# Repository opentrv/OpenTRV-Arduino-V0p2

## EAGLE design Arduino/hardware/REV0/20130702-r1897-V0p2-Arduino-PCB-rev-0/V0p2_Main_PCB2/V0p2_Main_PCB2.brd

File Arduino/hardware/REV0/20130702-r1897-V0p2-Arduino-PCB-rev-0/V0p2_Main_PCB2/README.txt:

Using ATmega pinout for Eagle from:
http://www.faludi.com/2008/10/07/arduino-avr-library-for-eagle-layout-editor/
without explicit licence but following email permission:

    From: Rob Faludi
    Date: 13 May 2013 00:34:52 GMT+01:00
    Subject: Re: A comment from Damon Hart-Davis
    
    Sure, go for it!
    
    A new submission (form: "Contact Form")
    ============================================
    Submitted on: May 12, 2013
    Via: /contact/
    
    --------------------------Contact Me----------------------
    
    Your Name:                      Damon Hart-Davis
    
    Message:                      
    May we use your Eagle ATmega package/library:
    
    http://www.faludi.com/2008/10/07/arduino-avr-library-for-eagle-layout-editor/
    
    In our Apache/Solderpad-licenced OpenTRV project please?
    
    Rgds
    
    Damon
    http://opentrv.org.uk/

Note ITEADstudio .dru and .cam files downloaded from their site AND NOT COVERED BY OUR APACHE LICENCE
though ITEADstudio would probably be happy for you to use their service like we did!

Component-ordering document:
https://docs.google.com/spreadsheet/ccc?key=0AkWwv0Q6wTaZdHkyZ0JmMVE3X1ExWGNqcHVxUUhROHc#gid=0

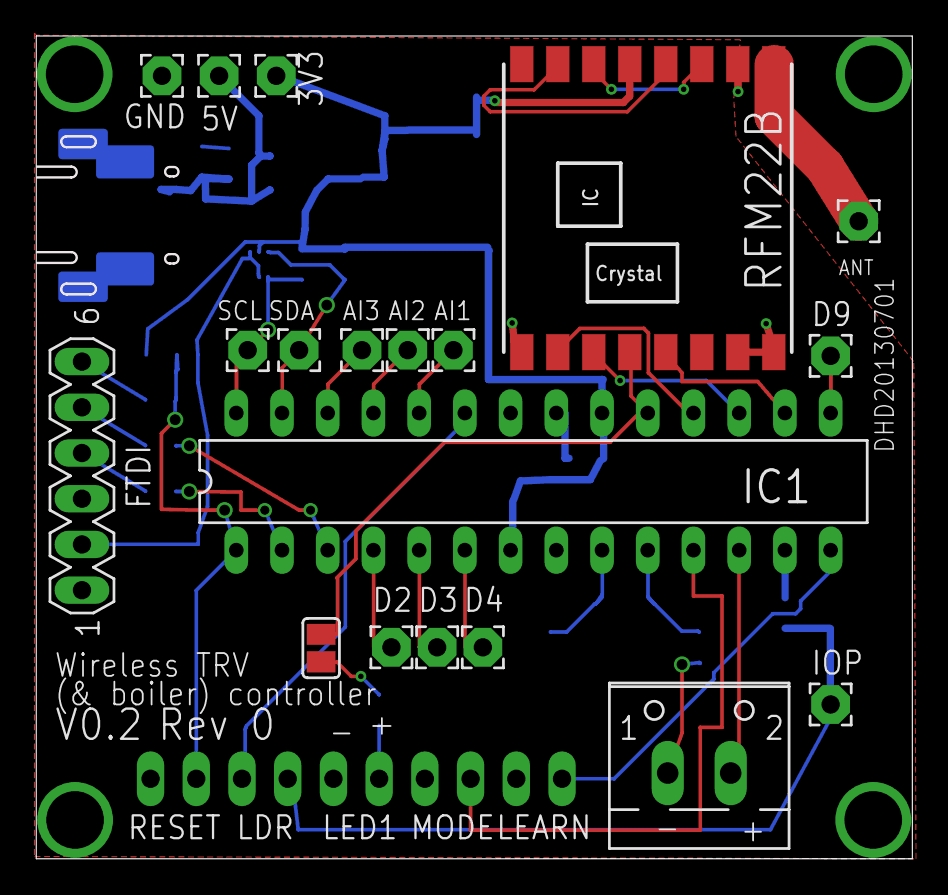
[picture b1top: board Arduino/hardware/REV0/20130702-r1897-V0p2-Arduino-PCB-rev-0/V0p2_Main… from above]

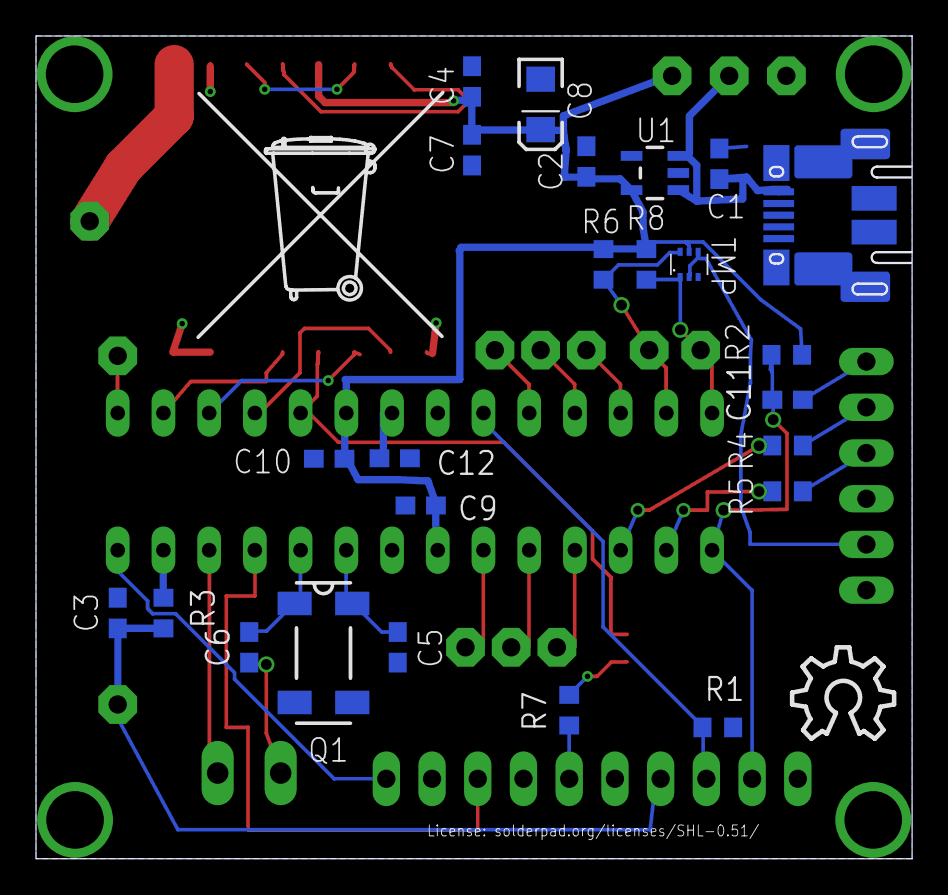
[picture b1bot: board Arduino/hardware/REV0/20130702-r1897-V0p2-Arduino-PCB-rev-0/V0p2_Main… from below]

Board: 2 copper layers, 48.7 x 45.7 mm, 50 parts (28 on the bottom side), 36 nets.

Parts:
3V3, 5V: 2,15/1,0
-: BOILER; SCREWTERMINAL
AI1, AI2, AI3: 2,15/1,0
ANT: ANT (86 mm); 2,15/1,0
C1, C2: 10uF 10V; 0603-CAP
C3, C7, C9, C10, C11, C12: 100nF; 0603-CAP
C4: 100pF; 0603-CAP
C5, C6: 0pF; 0603-CAP
C8: 100uF; EIA3216
D2, D3, D4, D9: 2,15/1,0
FTDI: FTDI; MA06-1
GND: 2,15/1,0
IC1: ATMEGA328P-PU; DIL28-3
IOP: 2,15/1,0
JP1: MICRO-USB-FCI-10103592
LDR: 1X02
LEARN: 1X02
LED1: 1X02
MODE: 1X02
Q1: 32768Hz; MC-306
R1: 100K; R0603
R2, R4, R5: 10K; R0603
R3: 330R; R0603
R6, R8: 4K7; R0603
R7: 470R; R0603
RESET: 1X02
RFM22B: RFM22SMD; RFM22-XXX-S2
SCL: 2,15/1,0
SDA: 2,15/1,0
SJ1: SJ
TMP: TMP112
U1: TC1185SMD; TC1185
U$1: OSHW_10X200_NOTEXT
U$2: TONNE

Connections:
5V: 5V.1, C1.1, JP1.1, U1.1, U1.3
AI1: AI1.1, IC1.24
AI2: AI2.1, IC1.25
AI3: AI3.1, IC1.26
BOILER: -.2, IC1.12
BUTTON_LEARN_L: IC1.14, LEARN.1
BUTTON_MODE_L: IC1.11, MODE.1
D2: D2.1, IC1.4
D3: D3.1, IC1.5
D4: D4.1, IC1.6
D9: D9.1, IC1.15
GND: -.1, C1.2, C2.1, C3.1, C4.2, C5.2, C6.2, C7.1, C8.C, C9.2, C10.2, C12.2, FTDI.1, FTDI.2, GND.1, IC1.8, IC1.22, JP1.5, JP1.7, JP1.11, JP1.12, JP1.17, LEARN.2, LED1.1, MODE.2, R1.2, RESET.1, RFM22B.2, RFM22B.9, RFM22B.15, RFM22B.16, TMP.2, TMP.4, U1.2
IO_POWER: C3.2, IOP.1, LDR.2, R3.2
IO_POWER_UP: IC1.13, R3.1
LDR: IC1.23, LDR.1, R1.1
LEDEXT: LED1.2, R7.2
LED_HEATCALL: R7.1, SJ1.2
unnamed: C11.2, FTDI.6
unnamed: FTDI.4, R5.2
unnamed: FTDI.5, R4.2
unnamed: C12.1, IC1.21
unnamed: RFM22B.3, RFM22B.6
unnamed: RFM22B.4, RFM22B.7
unnamed: ANT.1, RFM22B.1
RESET: C11.1, IC1.1, R2.2, RESET.2
RX: IC1.3, R4.1
SCL: IC1.28, R8.1, SCL.1, TMP.1
SDA: IC1.27, R6.2, SDA.1, TMP.6
SPI_MISO: IC1.18, RFM22B.10
SPI_MOSI: IC1.17, RFM22B.11
SPI_NSS: IC1.16, RFM22B.13
SPI_SCK: IC1.19, RFM22B.12, SJ1.1
TX: IC1.2, R5.1
VCC: 3V3.1, C2.2, C4.1, C7.2, C8.A, C9.1, C10.1, IC1.7, IC1.20, R2.1, R6.1, R8.2, RFM22B.5, TMP.5, U1.5
XTAL1: C5.1, IC1.9, Q1.4
XTAL2: C6.1, IC1.10, Q1.1

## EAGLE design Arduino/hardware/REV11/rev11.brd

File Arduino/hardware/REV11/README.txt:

REV 11 is RFM23B and phototransistor and SHT21, with no UI eg neither buttons nor LEDs.
Light-weight passive sensor, eg for baseline and general monitoring/measurement in homes.
Senses/reports: ambient light, temperature, relative humidity (plus battery voltage and restarts).
Powered by AAA cells to save space, and designed to fit into a relatively discreet small vented plastic case.

Target box: http://m.rapidonline.com/mechanical-fastenings-fixings/low-profile-sensor-case-white-30-3226

(Note: board is smaller than the maximum possible.)

Note ITEADstudio .dru and .cam files downloaded from their site AND NOT COVERED BY OUR APACHE LICENCE
though ITEADstudio would probably be happy for you to use their service like we did!

Some testing notes:
http://www.earth.org.uk/OpenTRV/test/201601-REV7-REV10-REV11-HardwareTesting-DE.pdf

Component-ordering document: https://docs.google.com/spreadsheets/d/1gsCwtDZDTSBvkgDIGdEZPMJ3iMatSaSa38pdLNWTiDY/edit#gid=0

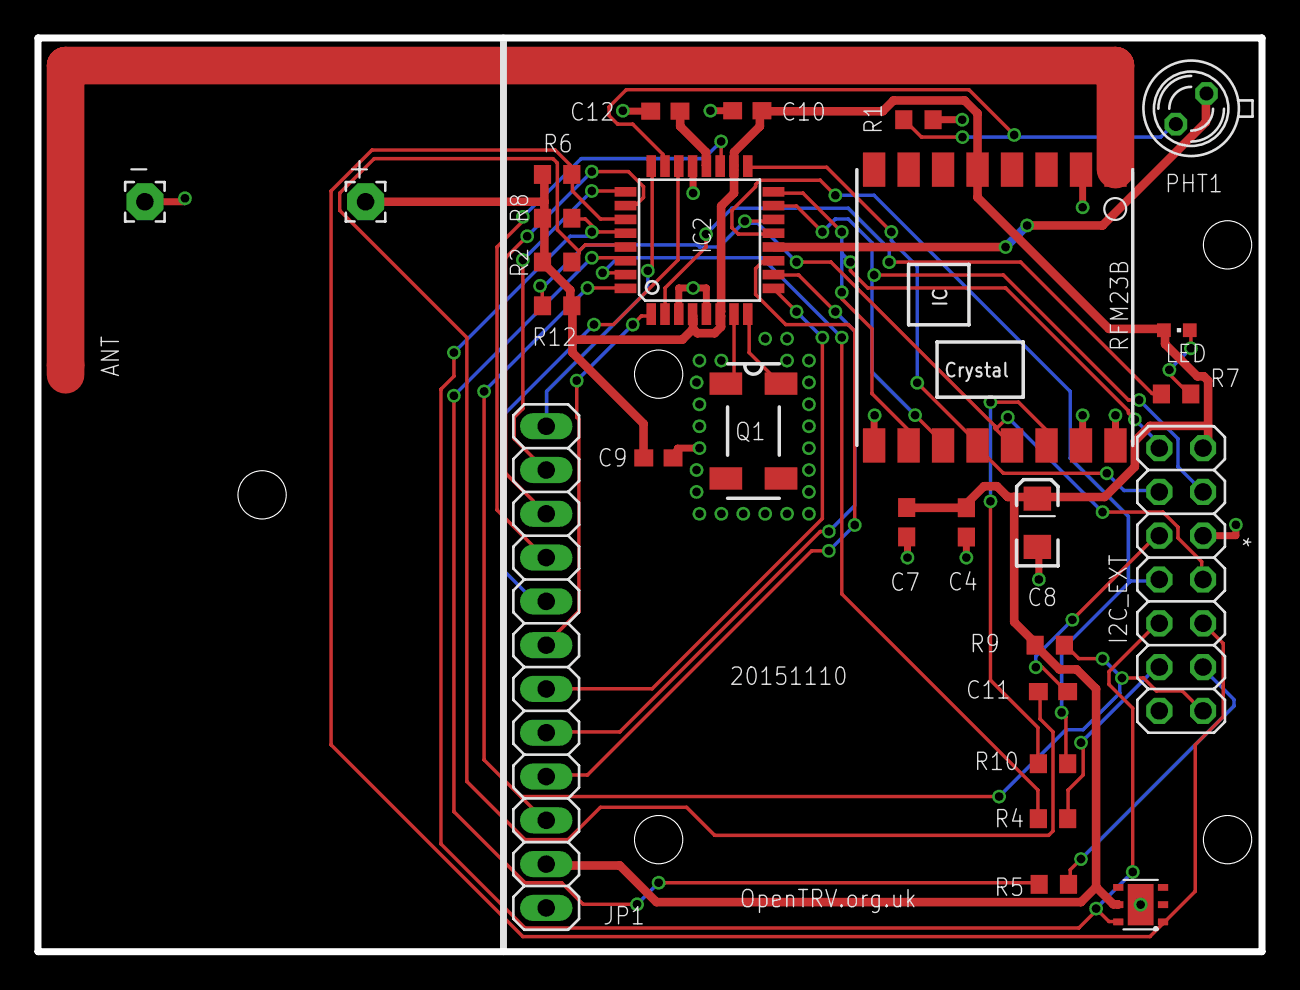
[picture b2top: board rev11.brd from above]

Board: 2 copper layers, 71.0 x 53.0 mm, 30 parts (0 on the bottom side), 34 nets.

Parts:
+: 2,15/1,0
-: 2,15/1,0
ANT: SMD1,27-2,54
C4: 100pF; C0603
C7, C9, C10, C11, C12: 100nF; C0603
C8: 100uF; EIA3216
I2C_EXT: 2X07
IC2: ATMEGA168-AU; TQFP32-08
JP1: 1X12
LED: CHIPLED_0603
PHT1: BPX65
Q1: 32768Hz; MC-306
R1: 100K; R0603
R2, R4, R5, R6, R8, R9, R12: 4.7K; R0603
R7: 470R; R0603
R10: 1K; R0603
RFM23B: RFM23B; RFM23-XXX-S1
U$1: OSHW_10X200_NOTEXT
U$2: TONNE
U$4: SHT21

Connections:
A1: IC2.24, JP1.1
A2: IC2.25, JP1.2
A3: IC2.26, JP1.3
A6: IC2.19, JP1.4
A7: IC2.22, JP1.5
D2: I2C_EXT.14, IC2.32, JP1.10, R9.1
D3: IC2.1, JP1.6
D5: IC2.9, JP1.7
D6: IC2.10, JP1.8
D7: IC2.11, JP1.9
GND: -.1, C4.1, C7.2, C8.C, C9.2, C10.2, C12.2, I2C_EXT.6, IC2.3, IC2.5, IC2.21, JP1.12, R1.2, RFM23B.2, RFM23B.9, RFM23B.15, RFM23B.16, U$4.2, U$4.P$1
IO_POWER_UP: IC2.12, PHT1.A
LDR: IC2.23, PHT1.K, R1.1
LED_HEATCALL_L: IC2.2, R7.1
unnamed: C11.2, I2C_EXT.5
unnamed: I2C_EXT.12, R5.2
unnamed: I2C_EXT.11, R4.2
unnamed: C12.1, IC2.20
unnamed: R10.2, RFM23B.14
unnamed: LED.C, R7.2
unnamed: ANT.1, RFM23B.1
RESET: C11.1, IC2.29, R2.2
RFM_IRQ: I2C_EXT.7, IC2.13, R10.1
RX: IC2.31, R4.1
SCL: I2C_EXT.9, IC2.28, R8.1, U$4.6
SDA: I2C_EXT.10, IC2.27, R6.2, U$4.1
SPI_MISO: I2C_EXT.1, IC2.16, RFM23B.10
SPI_MOSI: I2C_EXT.4, IC2.15, RFM23B.11
SPI_NSS: I2C_EXT.8, IC2.14, R12.1, RFM23B.13
SPI_SCK: I2C_EXT.3, IC2.17, RFM23B.12
TX: IC2.30, R5.1
VCC: +.1, C4.2, C7.1, C8.A, C9.1, C10.1, I2C_EXT.2, IC2.4, IC2.6, IC2.18, JP1.11, LED.A, R2.1, R6.1, R8.2, R9.2, R12.2, RFM23B.5, U$4.5
XTAL1: IC2.8, Q1.4
XTAL2: IC2.7, Q1.1

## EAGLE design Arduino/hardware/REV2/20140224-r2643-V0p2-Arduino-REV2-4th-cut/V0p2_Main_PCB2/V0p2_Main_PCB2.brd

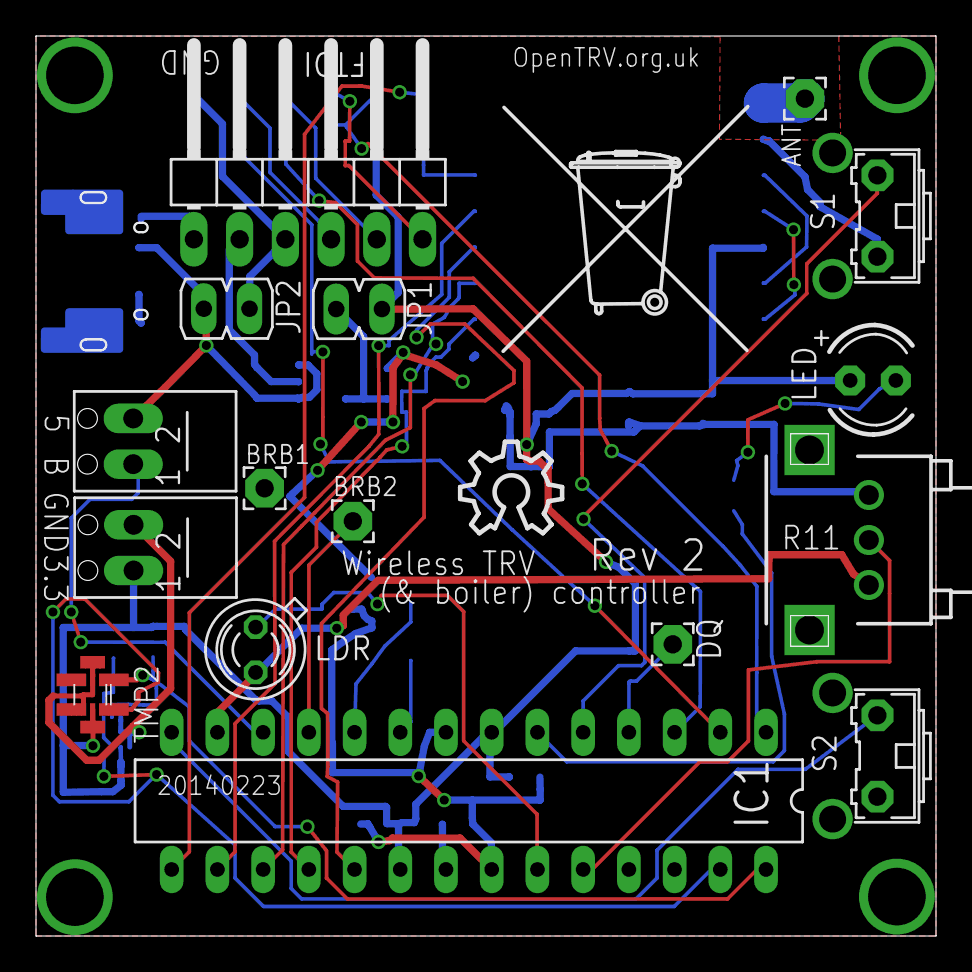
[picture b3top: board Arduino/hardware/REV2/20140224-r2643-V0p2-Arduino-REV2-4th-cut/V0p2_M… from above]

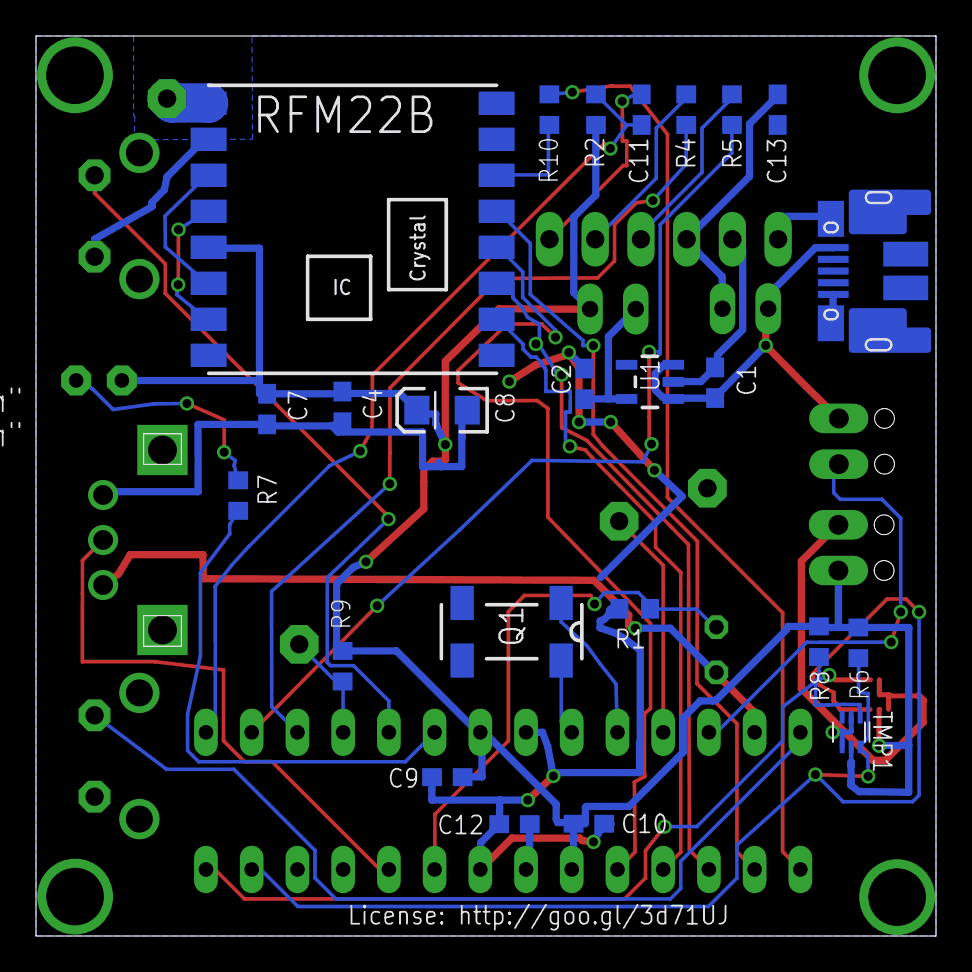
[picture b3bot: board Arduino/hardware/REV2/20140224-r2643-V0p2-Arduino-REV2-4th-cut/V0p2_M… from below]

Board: 2 copper layers, 50.0 x 50.0 mm, 42 parts (24 on the bottom side), 35 nets.

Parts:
ANT: ANT (86 mm); 2,15/1,0
BRB1: BRB1; 2,15/1,0
BRB2: BRB2; 2,15/1,0
C1, C2, C13: 10uF 10V; 0603-CAP
C4: 100pF; 0603-CAP
C7, C9, C10, C11, C12: 100nF; 0603-CAP
C8: 100uF; EIA3216
DQ: 2,15/1,0
FTDI: 1X06/90
IC1: ATMEGA328P-PU; DIL28-3
JP1, JP2: JP1
LDR: BPX65
LED: LED3MM
Q1: 32768Hz; MC-306
R1: 100K; R0603
R2, R4, R5: 10K; R0603
R6, R8: 4K7; R0603
R7: 470R; R0603
R9: 4.7K; R0603
R10: 1K; R0603
R11: EVUE2A; EVUE
RFM22B: RFM22SMD; RFM22-XXX-S2
S1, S2: B3F-31XX
TMP1: TMP1; TMP112
TMP2: TMP2; TMP112
U1: TC1185SMD; TC1185
U$1: OSHW_10X200_NOTEXT
U$2: TONNE
USBPOWER: MICRO-USB-FCI-10103592
X1, X2: SCREWTERMINAL

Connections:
5V: C1.1, JP2.2, U1.1, U1.3, USBPOWER.1, X1.2
AI1: IC1.24, R11.2
BOILER: IC1.12, X1.1
BUTTON_LEARN2_L: IC1.5, S1.2
BUTTON_LEARN_L: IC1.14, S2.2
BUTTON_MODE_L: BRB2.1, IC1.11
D2: DQ.1, IC1.4, R9.1
GND: BRB1.1, C1.2, C2.1, C4.2, C7.1, C8.C, C9.2, C10.2, C12.2, C13.1, FTDI.1, FTDI.2, IC1.8, IC1.22, R1.2, R11.3, RFM22B.2, RFM22B.9, RFM22B.15, RFM22B.16, S1.1, S2.1, TMP1.2, TMP1.4, TMP2.2, TMP2.4, U1.2, USBPOWER.5, USBPOWER.7, USBPOWER.17, X2.2
IO_POWER_UP: IC1.13, LDR.K, R11.1
LDR: IC1.23, LDR.A, R1.1
LED_HEATCALL_L: IC1.6, R7.1
unnamed: C11.2, FTDI.6
unnamed: FTDI.4, R5.2
unnamed: FTDI.5, R4.2
unnamed: C12.1, IC1.21
unnamed: R10.2, RFM22B.14
unnamed: C2.2, JP1.1, U1.5
unnamed: C13.2, FTDI.3, JP2.1
unnamed: LED.K, R7.2
unnamed: RFM22B.3, RFM22B.6
unnamed: RFM22B.4, RFM22B.7
unnamed: ANT.1, RFM22B.1
RESET: C11.1, IC1.1, R2.2
RFM_IRQ: IC1.15, R10.1
RX: IC1.3, R4.1
SCL: IC1.28, R8.1, TMP1.1, TMP2.1
SDA: IC1.27, R6.2, TMP1.6, TMP2.6
SPI_MISO: IC1.18, RFM22B.10
SPI_MOSI: IC1.17, RFM22B.11
SPI_NSS: IC1.16, RFM22B.13
SPI_SCK: IC1.19, RFM22B.12
TX: IC1.2, R5.1
VCC: C4.1, C7.2, C8.A, C9.1, C10.1, IC1.7, IC1.20, JP1.2, LED.A, R2.1, R6.1, R8.2, R9.2, RFM22B.5, TMP1.5, TMP2.5, X2.1
XTAL1: IC1.9, Q1.4
XTAL2: IC1.10, Q1.1

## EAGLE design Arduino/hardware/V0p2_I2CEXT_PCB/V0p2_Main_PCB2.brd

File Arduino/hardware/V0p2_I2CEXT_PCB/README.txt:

I2C (and OW) Extension board, daisy-chain design, in standard 5x5 format.

Note ITEADstudio .dru and .cam files downloaded from their site AND NOT COVERED BY OUR APACHE LICENCE
though ITEADstudio would probably be happy for you to use their service like we did!

Component-ordering document:

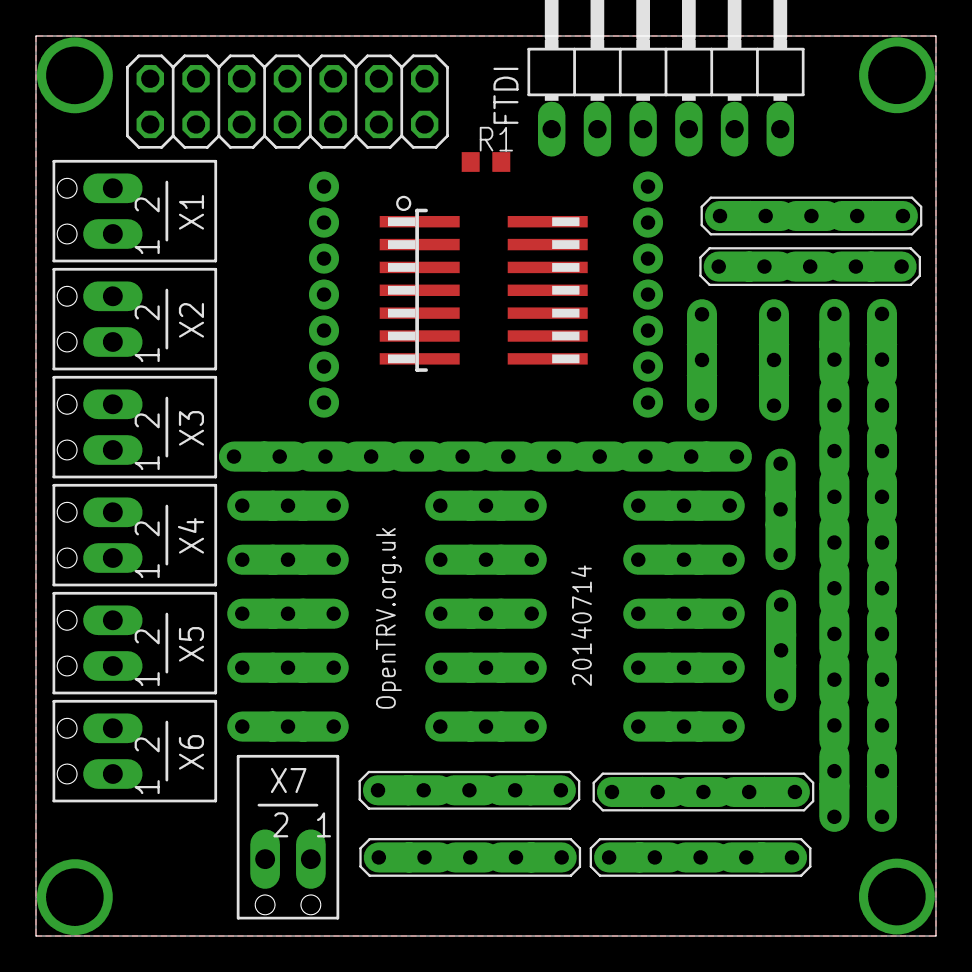
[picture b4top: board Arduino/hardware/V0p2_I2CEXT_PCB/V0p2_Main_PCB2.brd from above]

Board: 2 copper layers, 50.0 x 50.0 mm, 53 parts (0 on the bottom side), 28 nets, no tracks yet.

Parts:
FTDI: 1X06/90
GNDSTRIP1, GNDSTRIP4: 12-STRIP
IC1: SMD-14; SO-14NMW
JP1: 2X07
R1: 4.7K; R0603
U$1, U$4, U$7, U$16, U$24, U$36: 5-STRIP
U$2, U$6, U$8, U$9, U$19, U$25, U$27, U$34, U$35, U$37, U$38, U$39, U$40, U$41: PERF; PERFHOLE
U$5, U$10, U$11, U$12, U$13, U$14, U$15, U$17, U$18, U$26, U$30, U$32, U$33, U$43, U$44, U$45, U$46, U$47, U$48: 3-STRIP
VCCSTRIP2: 12-STRIP
X1, X2, X3, X4, X5, X6, X7: SCREWTERMINAL

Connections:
DQ: JP1.14, X7.1
GND: FTDI.1, JP1.6, R1.2, X3.1
unnamed: FTDI.2, R1.1
unnamed: IC1.P$1, U$2.P$1
unnamed: IC1.P$2, U$6.P$1
unnamed: IC1.P$3, U$8.P$1
unnamed: IC1.P$4, U$9.P$1
unnamed: IC1.P$5, U$19.P$1
unnamed: IC1.P$6, U$25.P$1
unnamed: IC1.P$7, U$27.P$1
unnamed: IC1.P$8, U$34.P$1
unnamed: IC1.P$9, U$35.P$1
unnamed: IC1.P$10, U$37.P$1
unnamed: IC1.P$11, U$38.P$1
unnamed: IC1.P$12, U$39.P$1
unnamed: IC1.P$13, U$40.P$1
unnamed: IC1.P$14, U$41.P$1
RESET: FTDI.6, X3.2
RFM_IRQ: JP1.7, X4.2
RXD0: FTDI.5, X6.2
SCL: JP1.9, X5.2
SDA: JP1.10, X5.1
SPI_MISO: JP1.1, X1.2
SPI_MOSI: JP1.4, X2.1
SPI_NSS: JP1.8, X4.1
SPI_SCK: JP1.3, X2.2
TXD0: FTDI.4, X6.1
VCC: FTDI.3, JP1.2, X1.1

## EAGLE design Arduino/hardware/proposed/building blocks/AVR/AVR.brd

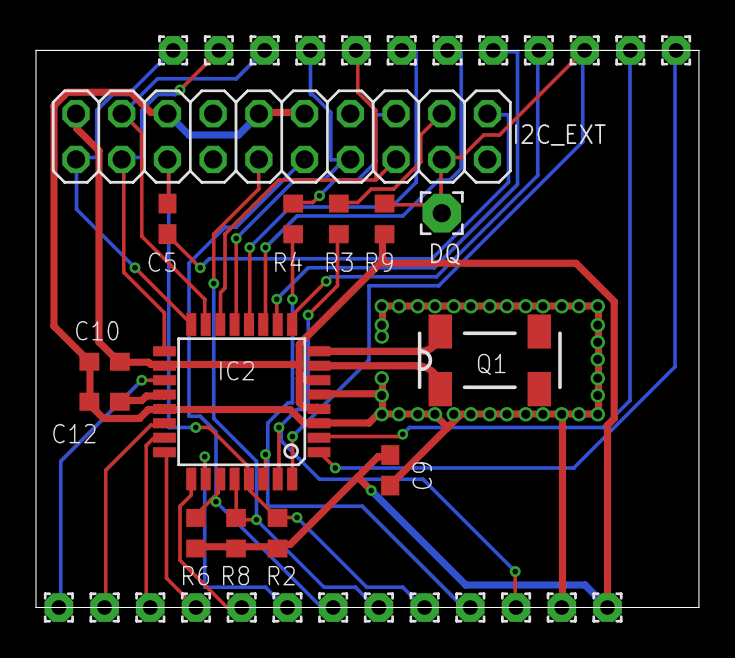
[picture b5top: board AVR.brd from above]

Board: 2 copper layers, 36.8 x 30.9 mm, 39 parts (0 on the bottom side), 31 nets.

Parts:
C5, C9, C10, C12: 100nF; C0603
DQ: 2,15/1,0
I2C_EXT: 2X10
IC2: ATMEGA168-AU; TQFP32-08
PAD1, PAD2, PAD3, PAD4, PAD5, PAD6, PAD7, PAD8, PAD9, PAD10, PAD11, PAD12, PAD13, PAD14, PAD15, PAD16, PAD17, PAD18, PAD19, PAD20, PAD21, PAD22, PAD23, PAD24, PAD25: 1,6/0,8
Q1: 32768Hz; MC-306
R2, R3, R4, R6, R8, R9: 4.7K; R0603

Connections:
D2: DQ.1, I2C_EXT.17, IC2.32, PAD14.1, R9.1
GND: C9.2, C10.2, C12.2, I2C_EXT.6, I2C_EXT.10, I2C_EXT.12, IC2.3, IC2.5, IC2.21, PAD2.1
unnamed: I2C_EXT.18, R3.2
unnamed: IC2.23, PAD4.1
unnamed: I2C_EXT.16, R4.2
unnamed: C5.2, I2C_EXT.20
unnamed: IC2.24, PAD5.1
unnamed: C12.1, IC2.20
unnamed: IC2.25, PAD6.1
unnamed: IC2.19, PAD10.1
unnamed: IC2.1, PAD15.1
unnamed: IC2.2, PAD16.1
unnamed: IC2.9, PAD17.1
unnamed: IC2.10, PAD18.1
unnamed: IC2.11, PAD19.1
unnamed: IC2.26, PAD7.1
unnamed: IC2.22, PAD11.1
unnamed: IC2.12, PAD20.1
RESET: C5.1, I2C_EXT.5, IC2.29, PAD1.1, R2.2
RFM_IRQ: I2C_EXT.13, IC2.13, PAD21.1
RX: IC2.31, PAD13.1, R3.1
SCL: I2C_EXT.9, IC2.28, PAD9.1, R8.1
SDA: I2C_EXT.11, IC2.27, PAD8.1, R6.2
SPI_MISO: I2C_EXT.1, IC2.16, PAD24.1
SPI_MOSI: I2C_EXT.4, IC2.15, PAD23.1
SPI_NSS: I2C_EXT.15, IC2.14, PAD22.1
SPI_SCK: I2C_EXT.3, IC2.17, PAD25.1
TX: IC2.30, PAD12.1, R4.1
VCC: C9.1, C10.1, I2C_EXT.2, IC2.4, IC2.6, IC2.18, PAD3.1, R2.1, R6.1, R8.2, R9.2
XTAL1: IC2.8, Q1.4
XTAL2: IC2.7, Q1.1

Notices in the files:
Arduino/hardware/REV0/20130702-r1897-V0p2-Arduino-PCB-rev-0/V0p2_Main_PCB2/V0p2_Main_PCB2.brd:
License: solderpad.org/licenses/SHL-0.51
Arduino/hardware/REV11/rev11.brd:
License: http://goo.gl/3d71UJ
parts and their libraries:
SparkFun-Passives: Licensing: CC v3.0 Share-Alike You are welcome to use this library for commercial purposes.
